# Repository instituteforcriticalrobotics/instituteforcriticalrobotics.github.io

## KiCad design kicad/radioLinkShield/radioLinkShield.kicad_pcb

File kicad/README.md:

Here we will store all our KiCad files

Change log 

10 Sep 2023 - ms - moved nRFControlPanel to
 https://github.com/michaelshiloh/resourcesForClasses/tree/master/kicad/nRFControlPanel

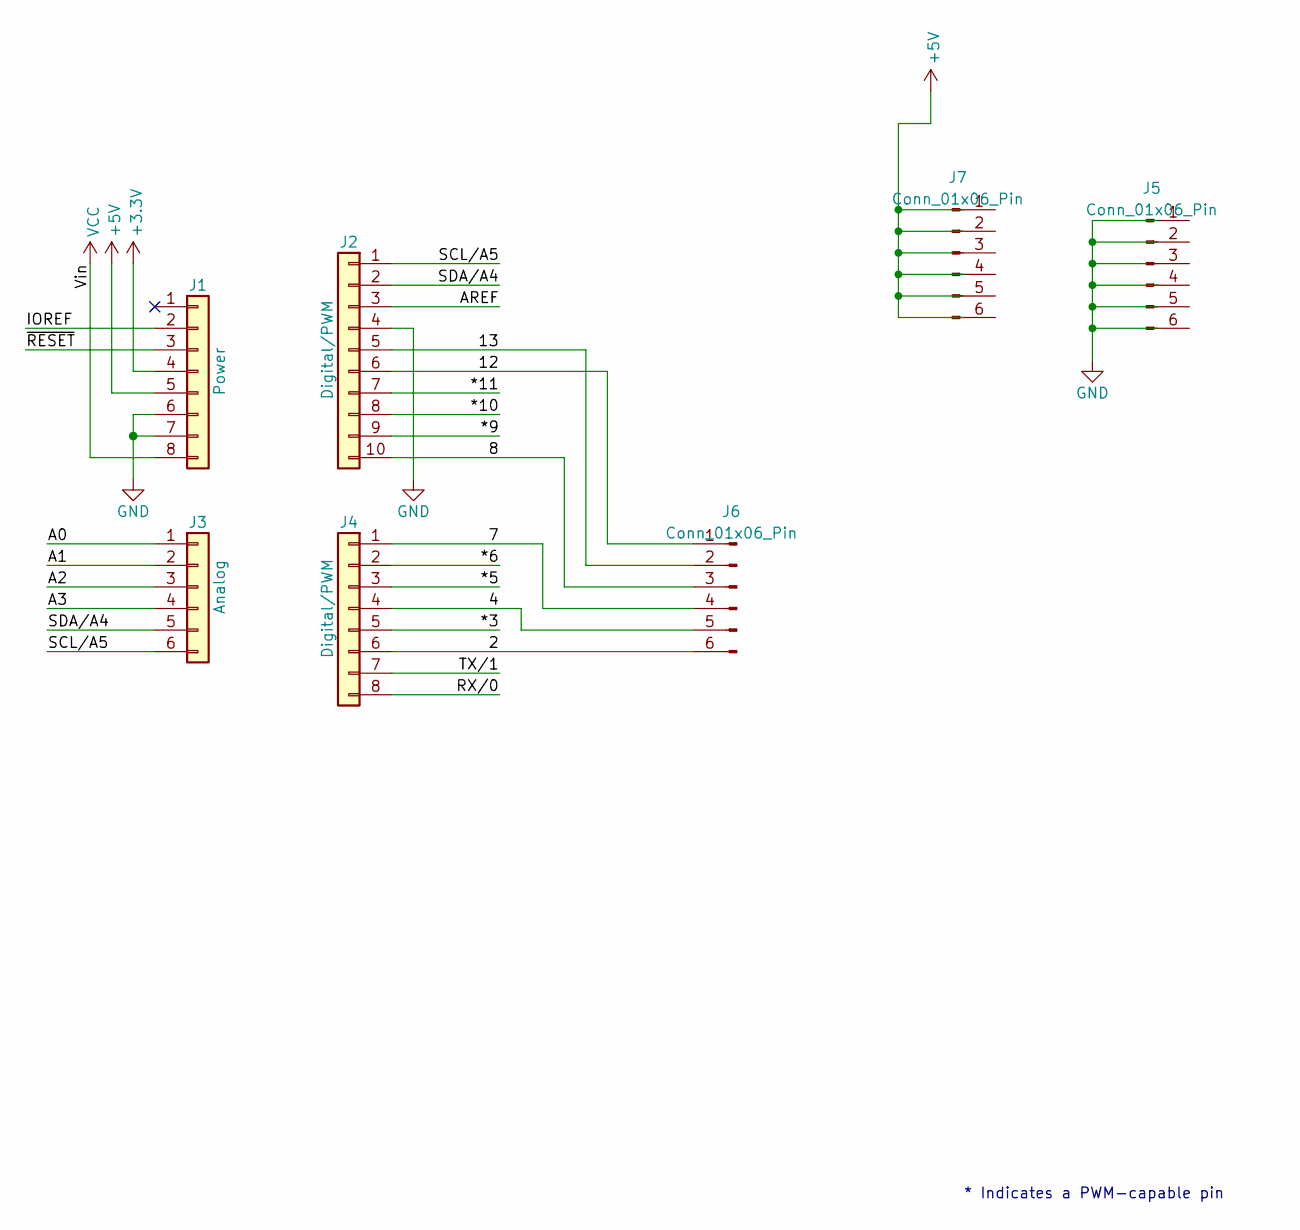
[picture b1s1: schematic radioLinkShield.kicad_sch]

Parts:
J1: Power; PinSocket_1x08_P2.54mm_Vertical
J2: Digital/PWM; PinSocket_1x10_P2.54mm_Vertical
J3: Analog; PinSocket_1x06_P2.54mm_Vertical
J4: Digital/PWM; PinSocket_1x08_P2.54mm_Vertical
J5, J6, J7: Conn_01x06_Pin; PinSocket_1x06_P2.54mm_Vertical

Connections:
+3V3: J1.4
+5V: J1.5
/2: J4.6, J6.6
/4: J4.4, J6.5
/7: J4.1, J6.4
/8: J2.10, J6.3
/12: J2.6, J6.1
/13: J2.5, J6.2
/*3: J4.5
/*5: J4.3
/*6: J4.2
/*9: J2.9
/*10: J2.8
/*11: J2.7
/A0: J3.1
/A1: J3.2
/A2: J3.3
/A3: J3.4
/AREF: J2.3
/IOREF: J1.2
/RX/0: J4.8
/SCL/A5: J2.1, J3.6
/SDA/A4: J2.2, J3.5
/TX/1: J4.7
/~RESET: J1.3
VCC: J1.8

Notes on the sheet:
* Indicates a PWM-capable pin

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
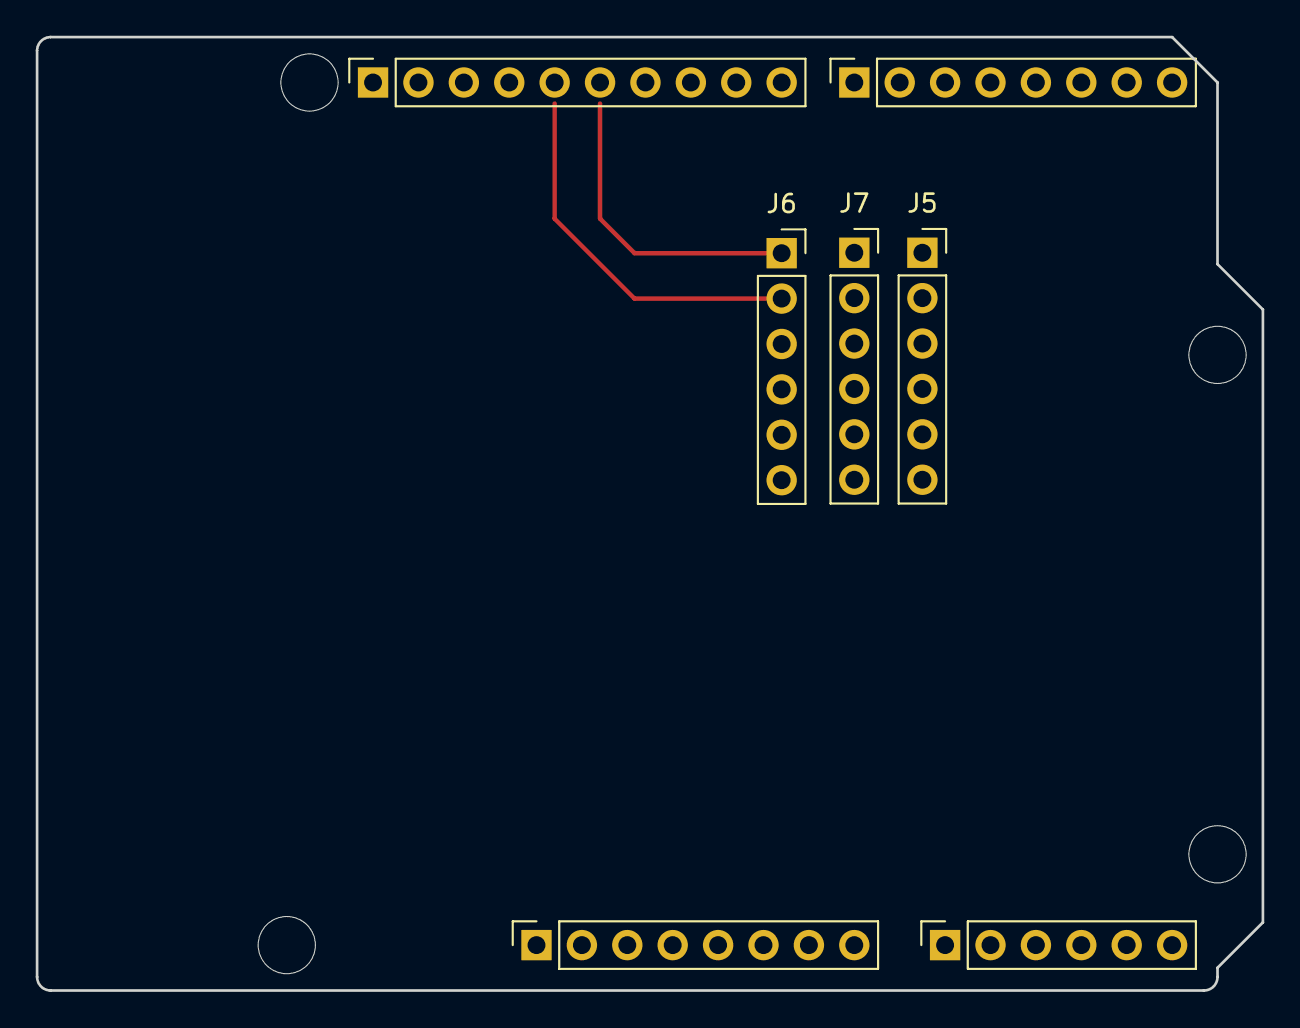
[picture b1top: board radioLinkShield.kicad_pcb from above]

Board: 2 copper layers, 68.6 x 53.3 mm, 11 parts (0 on the bottom side), 9 nets.

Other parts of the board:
MH1, MH2, MH3, MH4: MountingHole_3.2mm

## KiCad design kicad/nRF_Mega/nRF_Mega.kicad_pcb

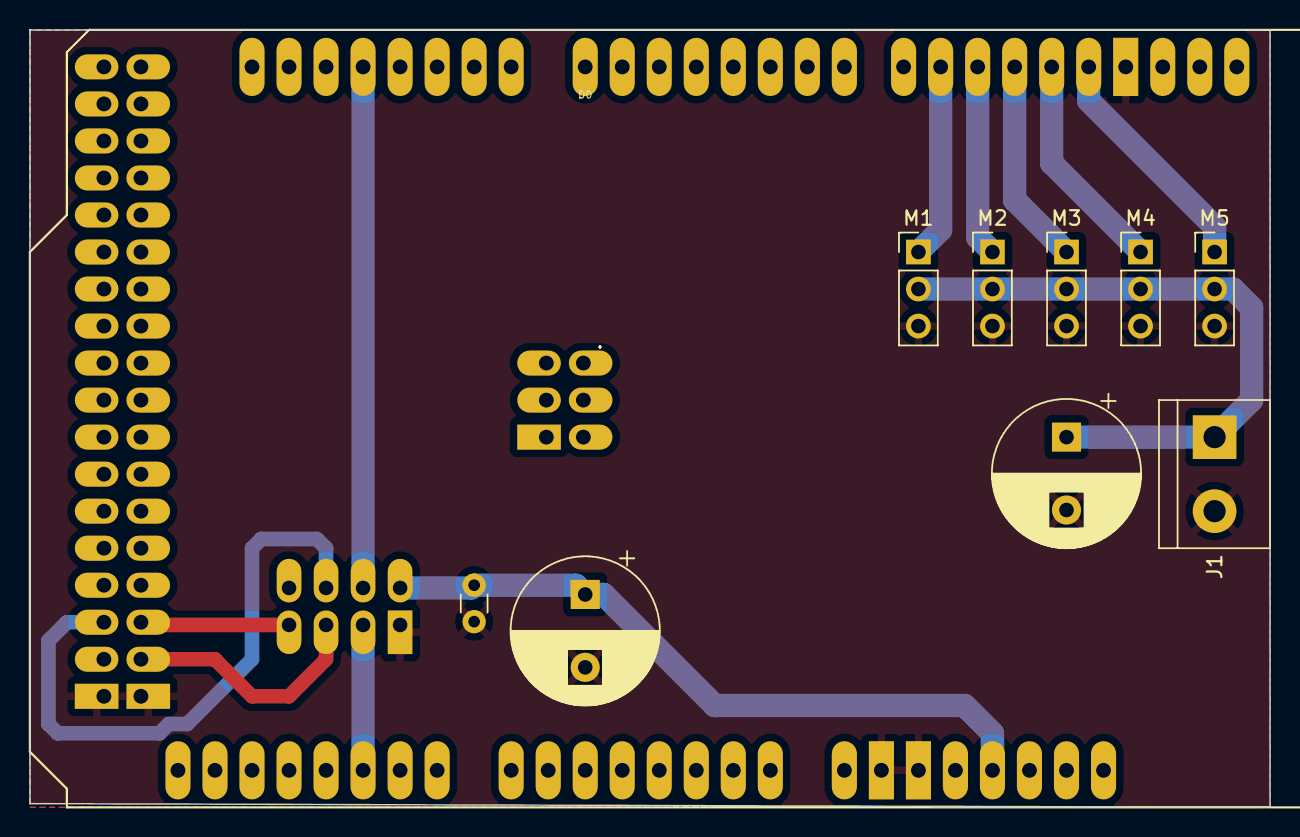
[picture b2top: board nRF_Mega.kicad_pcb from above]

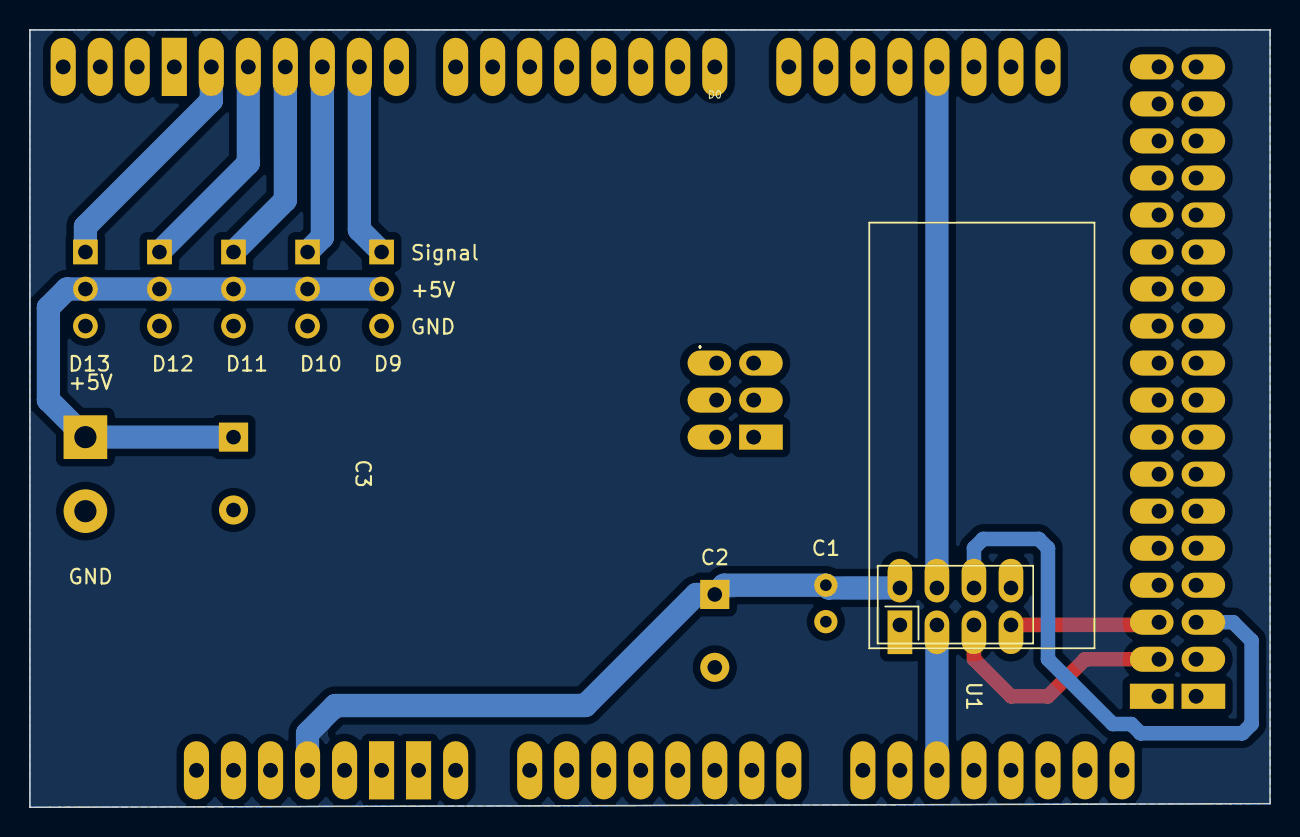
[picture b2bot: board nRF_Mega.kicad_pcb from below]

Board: 2 copper layers, 85.1 x 53.3 mm, 11 parts (2 on the bottom side), 13 nets.

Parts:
C1: .1 uF; C_Disc_D3.0mm_W1.6mm_P2.50mm
C2, C3: 470 uF; CP_Radial_D10.0mm_P5.00mm
J1: Screw_Terminal_01x02; TerminalBlock_bornier-2_P5.08mm
M1, M2, M3, M4, M5: Motor_Servo; PinHeader_1x03_P2.54mm_Vertical
U1: NRF24L01_Breakout; nRF24L01_Breakout
XA1: Arduino_Mega2560_Shield

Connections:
+3.3V: C1.1, C2.1, U1.2 (VCC), XA1.3V3 (3.3V)
GND: C1.2, C2.2, C3.2, J1.2, M1.3 (-), M2.3 (-), M3.3 (-), M4.3 (-), M5.3 (-), U1.1 (GND), XA1.GND1 (GND), XA1.GND2 (GND), XA1.GND3 (GND), XA1.GND5 (GND), XA1.GND6 (GND)
unnamed: C3.1, J1.1, M1.2 (+), M2.2 (+), M3.2 (+), M4.2 (+), M5.2 (+)
unnamed: M1.1 (PWM), XA1.D9
unnamed: M2.1 (PWM), XA1.D10
unnamed: M3.1 (PWM), XA1.D11
unnamed: M4.1 (PWM), XA1.D12
unnamed: M5.1 (PWM), XA1.D13
unnamed: U1.3 (CE), XA1.A10
unnamed: U1.7 (MISO), XA1.D50 (D50_MISO)
unnamed: U1.6 (MOSI), XA1.D51 (D51_MOSI)
unnamed: U1.5 (SCK), XA1.D52 (D52_SCK)
unnamed: U1.4 (~CSN), XA1.D18 (D18/TX1)

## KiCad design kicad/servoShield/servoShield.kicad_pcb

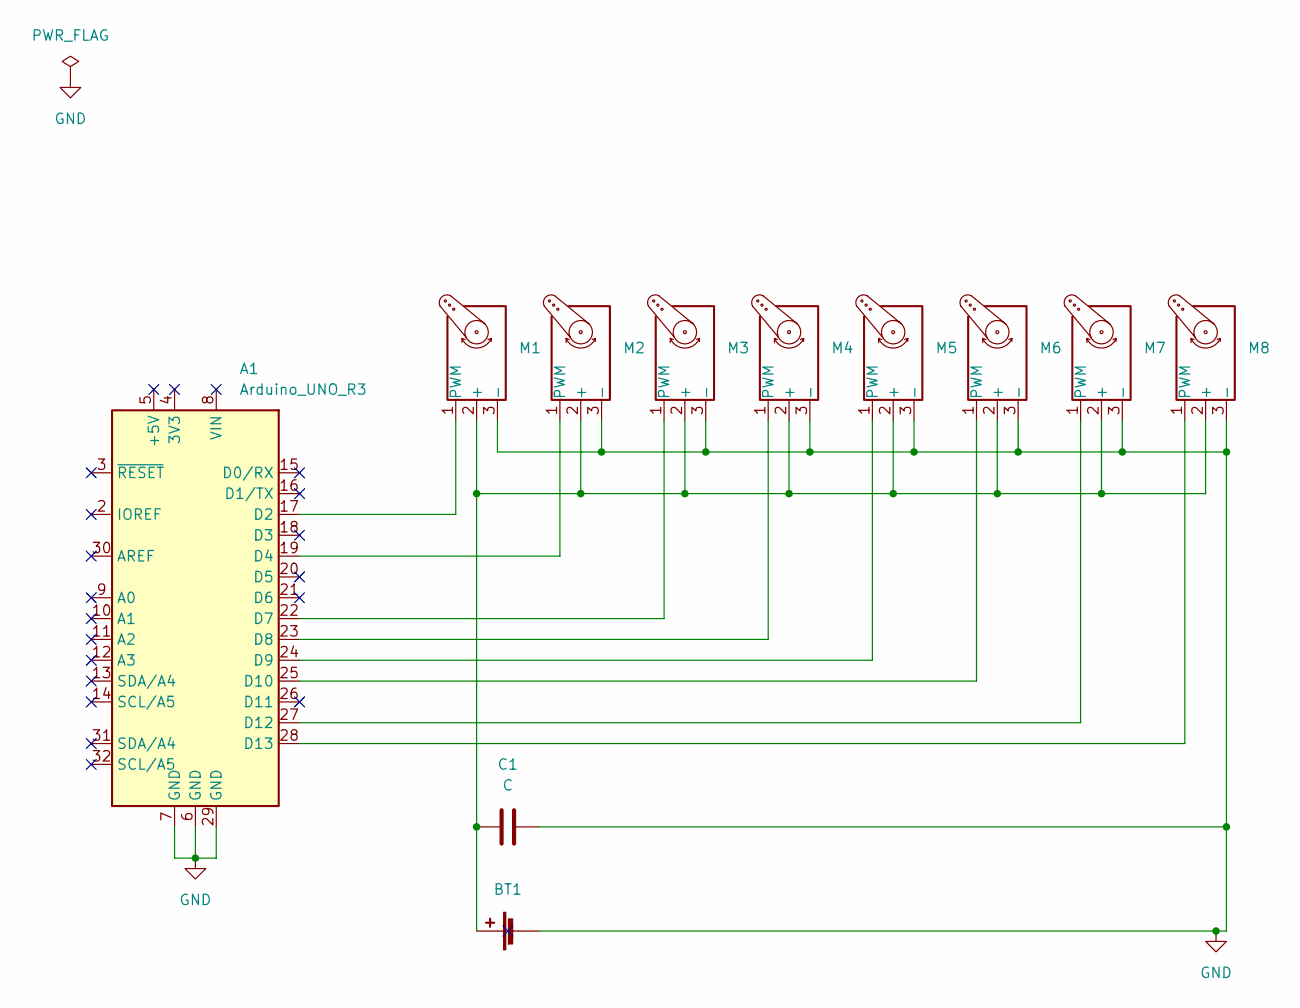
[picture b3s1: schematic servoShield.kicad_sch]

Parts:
A1: Arduino_UNO_R3
BT1: Battery_Cell; TerminalBlock_Phoenix_MKDS-1,5-2-5.08_1x02_P5.08mm_Horizont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
C1: C; CP_Radial_D10.0mm_P5.00mm
M1, M2, M3, M4, M5, M6, M7, M8: Motor_Servo; PinHeader_1x03_P2.54mm_Vertical

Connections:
GND: A1.6 (GND), A1.7 (GND), A1.29 (GND), BT1.2 (-), C1.2, M1.3 (-), M2.3 (-), M3.3 (-), M4.3 (-), M5.3 (-), M6.3 (-), M7.3 (-), M8.3 (-)
unnamed: A1.17 (D2), M1.1 (PWM)
unnamed: A1.19 (D4), M2.1 (PWM)
unnamed: A1.22 (D7), M3.1 (PWM)
unnamed: A1.23 (D8), M4.1 (PWM)
unnamed: A1.24 (D9), M5.1 (PWM)
unnamed: A1.25 (D10), M6.1 (PWM)
unnamed: A1.27 (D12), M7.1 (PWM)
unnamed: A1.28 (D13), M8.1 (PWM)
unnamed: BT1.1 (+), C1.1, M1.2 (+), M2.2 (+), M3.2 (+), M4.2 (+), M5.2 (+), M6.2 (+), M7.2 (+), M8.2 (+)

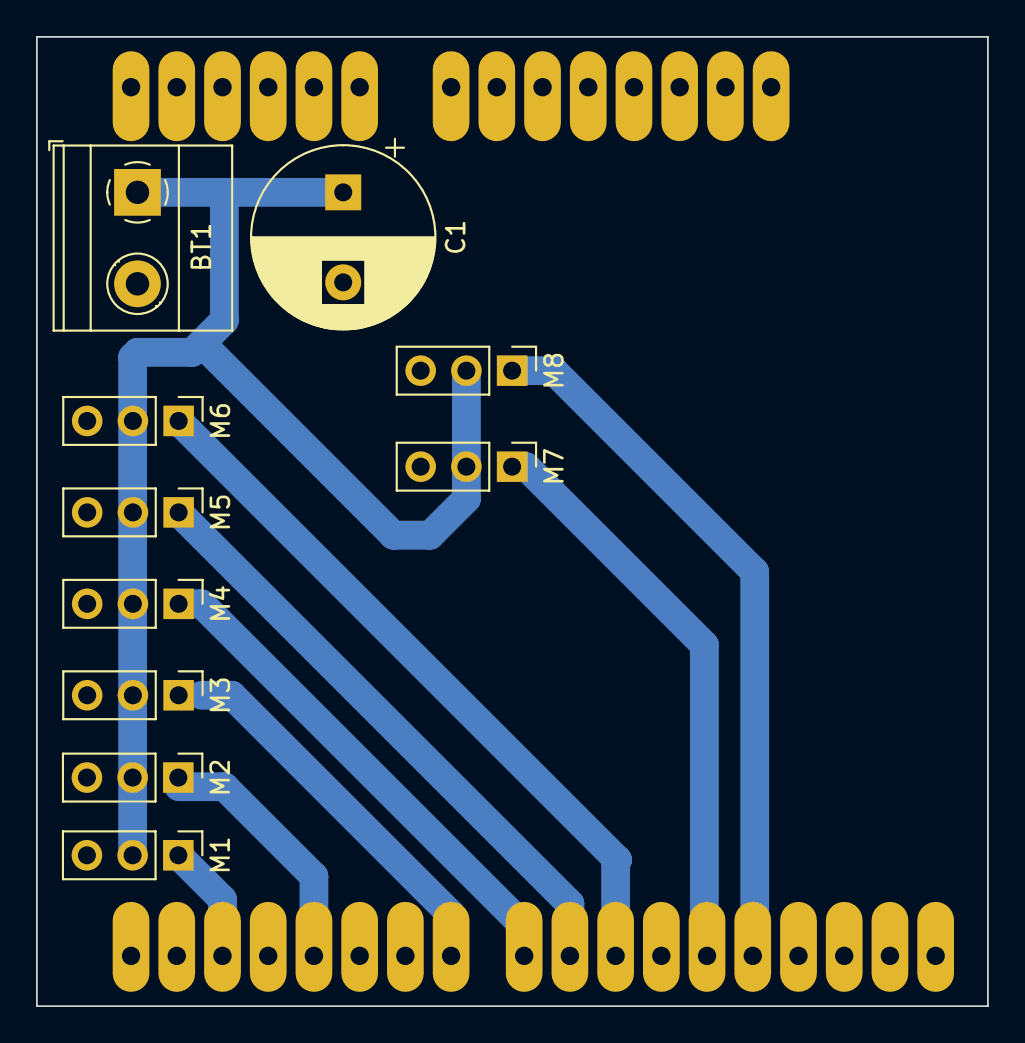
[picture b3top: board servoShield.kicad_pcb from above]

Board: 2 copper layers, 52.8 x 53.8 mm, 11 parts (1 on the bottom side), 10 nets.

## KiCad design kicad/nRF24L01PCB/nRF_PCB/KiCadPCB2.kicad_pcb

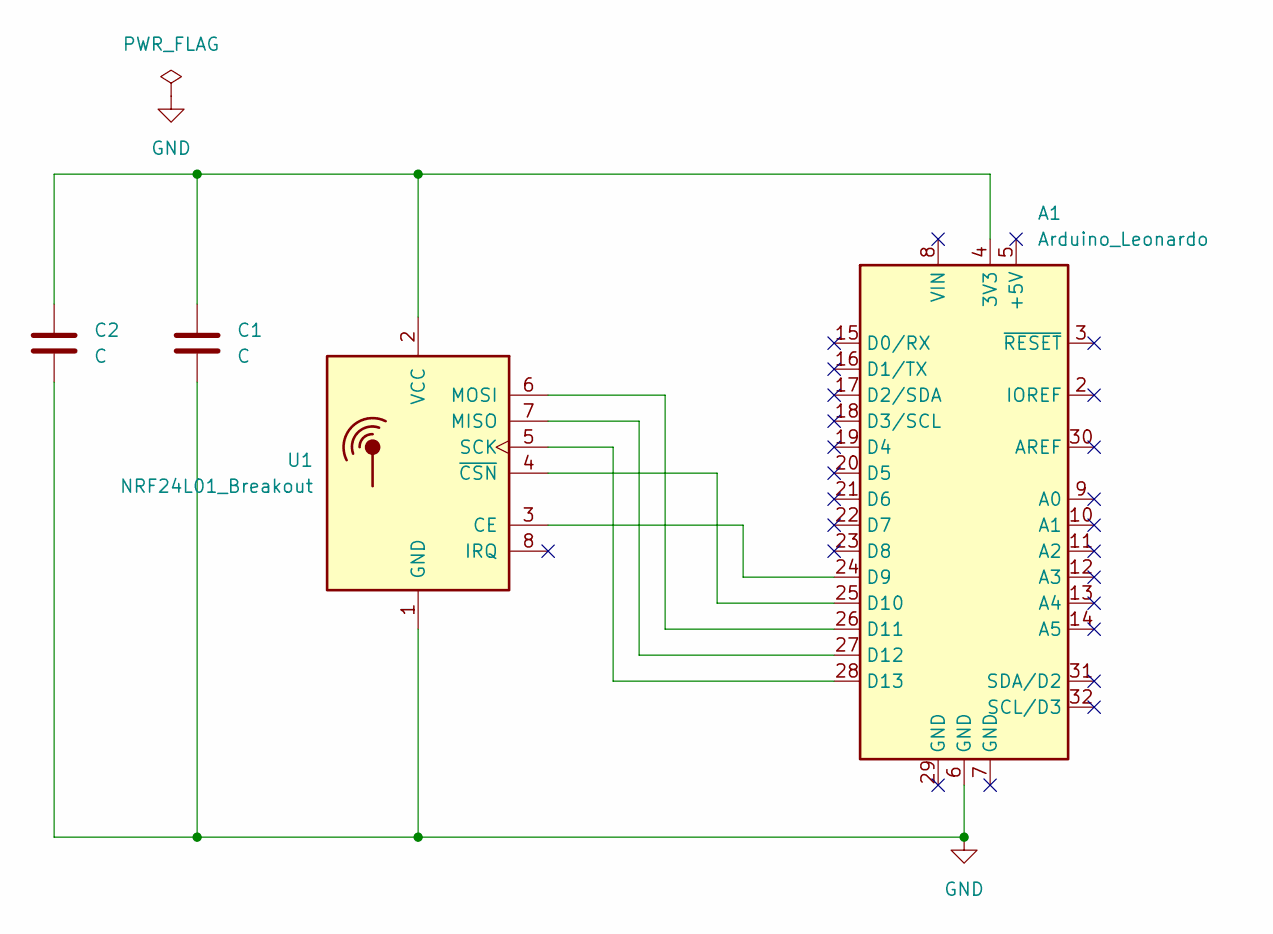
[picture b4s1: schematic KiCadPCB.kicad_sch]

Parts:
A1: Arduino_Leonardo; Arduino_UNO_R3
C1: C; CP_Radial_Tantal_D4.5mm_P2.50mm
C2: C; CP_Radial_D8.0mm_P5.00mm
U1: NRF24L01_Breakout; nRF24L01_Breakout

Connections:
GND: A1.6 (GND), C1.2, C2.2, U1.1 (GND)
unnamed: A1.4 (3V3), C1.1, C2.1, U1.2 (VCC)
unnamed: A1.24 (D9), U1.3 (CE)
unnamed: A1.25 (D10), U1.4 (~CSN)
unnamed: A1.26 (D11), U1.6 (MOSI)
unnamed: A1.27 (D12), U1.7 (MISO)
unnamed: A1.28 (D13), U1.5 (SCK)

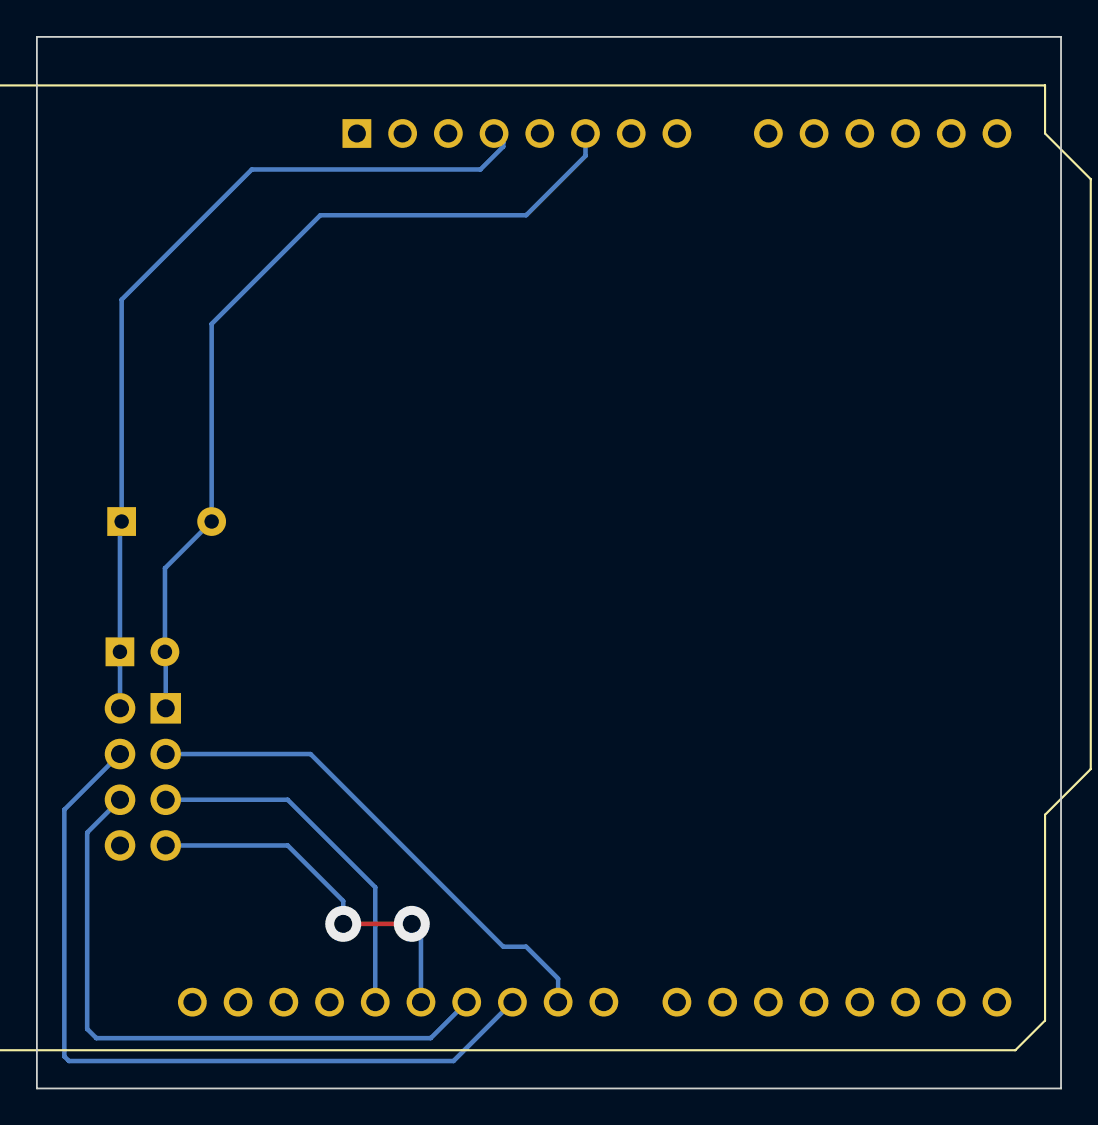
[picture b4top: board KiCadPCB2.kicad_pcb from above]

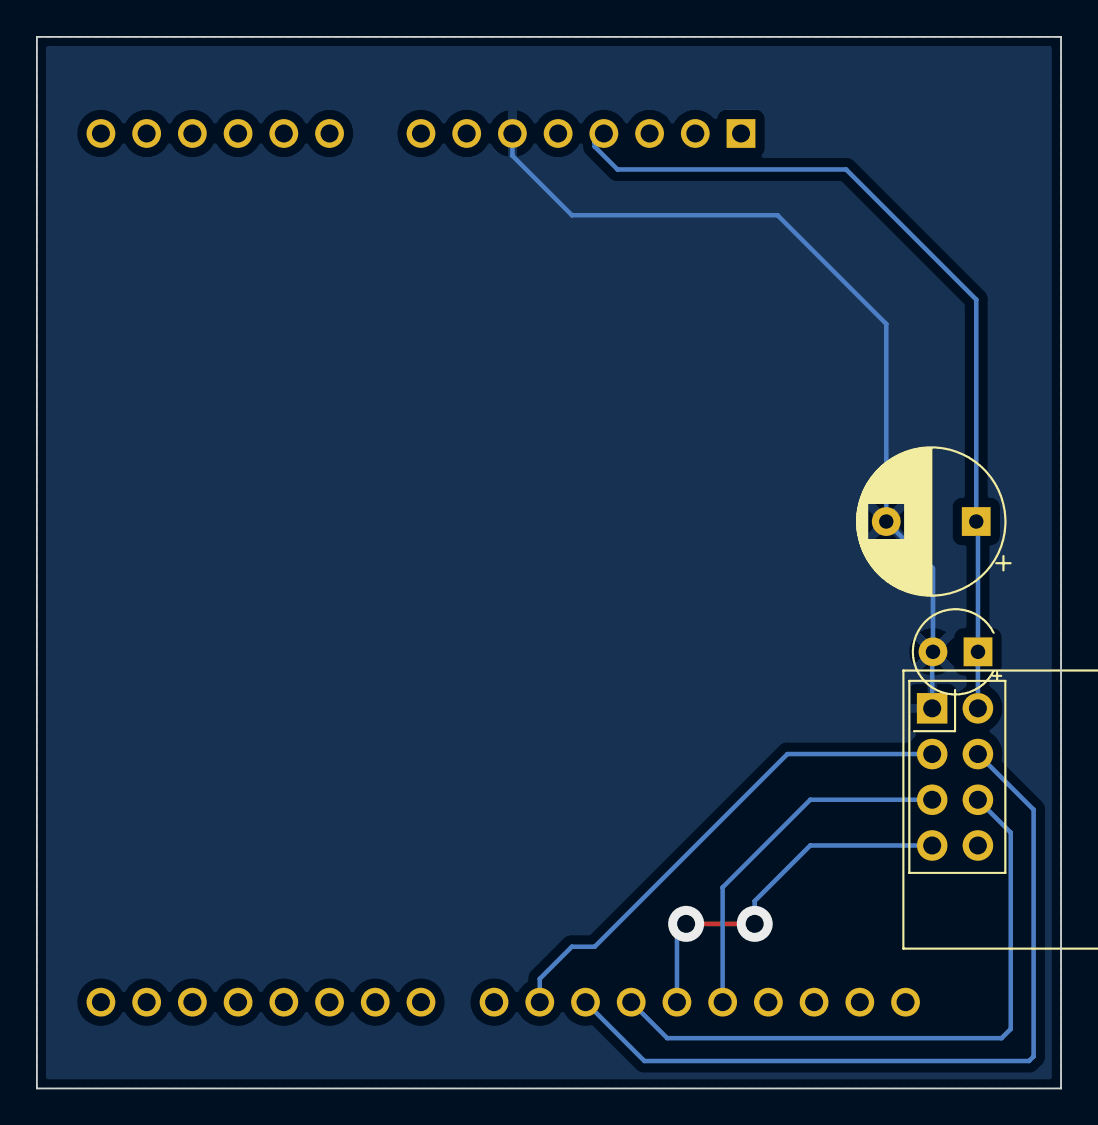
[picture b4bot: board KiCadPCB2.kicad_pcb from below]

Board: 2 copper layers, 56.9 x 58.4 mm, 4 parts (3 on the bottom side), 7 nets.

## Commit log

2022-09-18 Rename telepresence-updates.md to 2022-09-18-Telepresence-updates.md
2022-09-18 Create 2022-09-18
2022-09-18 Create 2022-09-18-Prototype-Shield-Documentation
2022-09-18 Rename 2022-09-18-Prototype-Shield-Documentation to 2022-09-18-Prototype-Shield-Documentation.md
2022-11-07 Create KiCad Instructions
2022-11-07 Update KiCad Instructions
2022-11-07 Rename KiCad Instructions to 2022-11-05-KiCad-Instructions.md
2022-11-08 Create 2022-11-08-Robot-Wiring-Process
2022-12-03 Create robotMedia
2023-02-12 5 servo motors now!
2023-02-12 add .gitignore file to project
2023-02-12 removed zip file
2023-02-12 added servo shield
2023-02-12 added .gitignore to the servoShield
2023-02-12 added footprint library table
2023-02-12 added git attributes file
2023-02-12 created custom pads for arduino shield
2023-02-12 removed the kicad_prl file from the repo
2023-02-12 updated diary with what I did yesterday and today
2023-02-20 Create .nRF-Mega
2023-02-21 added a resources post
2023-02-21 added
2023-03-10 Create Code for PeopleBot - Jesper
2023-03-10 Rename Code for PeopleBot - Jesper to 2023-03-10 Code for PeopleBot - Jesper.md
2023-03-31 Update 2023-03-10-Code-for-PeopleBot-Jesper.md
    added code which does control the motor and reads the distance sensors also
2023-04-06 fixed files to ignore
2023-04-06 added folder for code
2023-08-11 corrected nRF placement, minimized wire length, fixed caps and connector
2023-08-11 added .gitignore file
2023-08-23 no changes; just kicad touching stuff
2023-08-26 added nrf control panel
2023-08-26 added radiolink shield
2023-09-10 more work on the schematic for the nRFControlPanel
2023-09-10 moved nRFControlPanel to https://github.com/michaelshiloh/resourcesForClasses/tree/master/kicad/nRFControlPanel
2023-09-10 corrected link in README
2023-09-29 edited wrong file by accident; restored original
2023-11-04 created source code from readme
2023-11-04 too many subdirectories
2023-11-11 fixed indentation
2023-11-11 added README.md
2023-11-11 cleaning up unused code
